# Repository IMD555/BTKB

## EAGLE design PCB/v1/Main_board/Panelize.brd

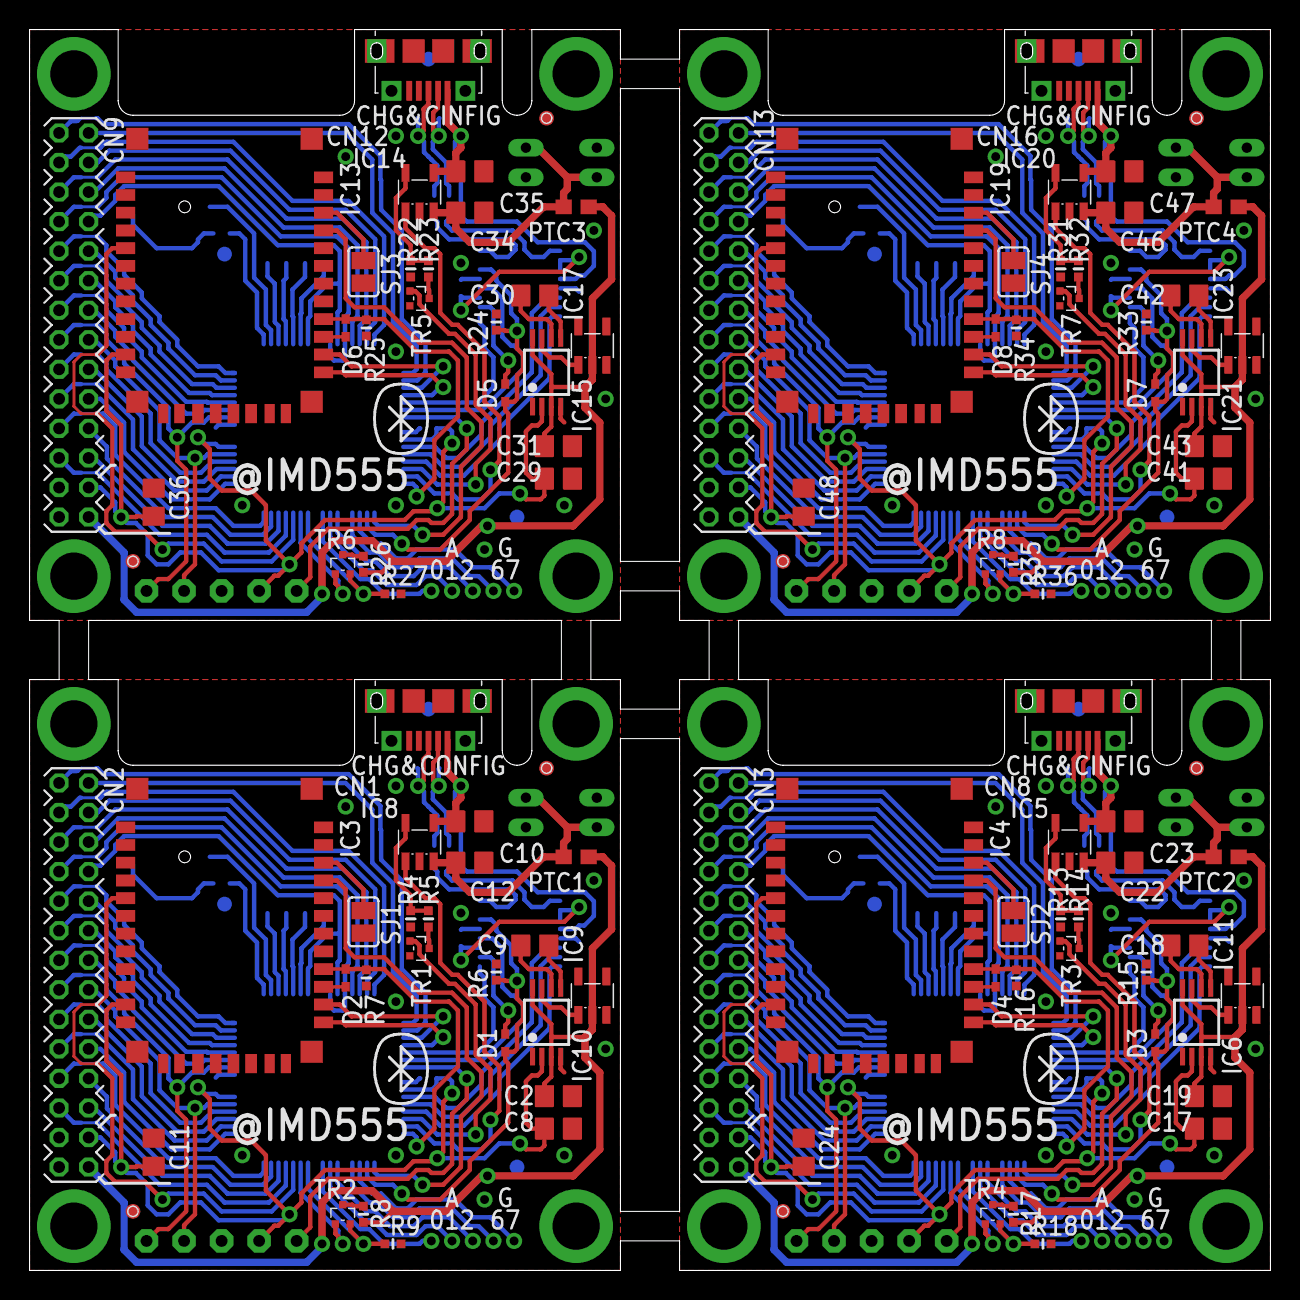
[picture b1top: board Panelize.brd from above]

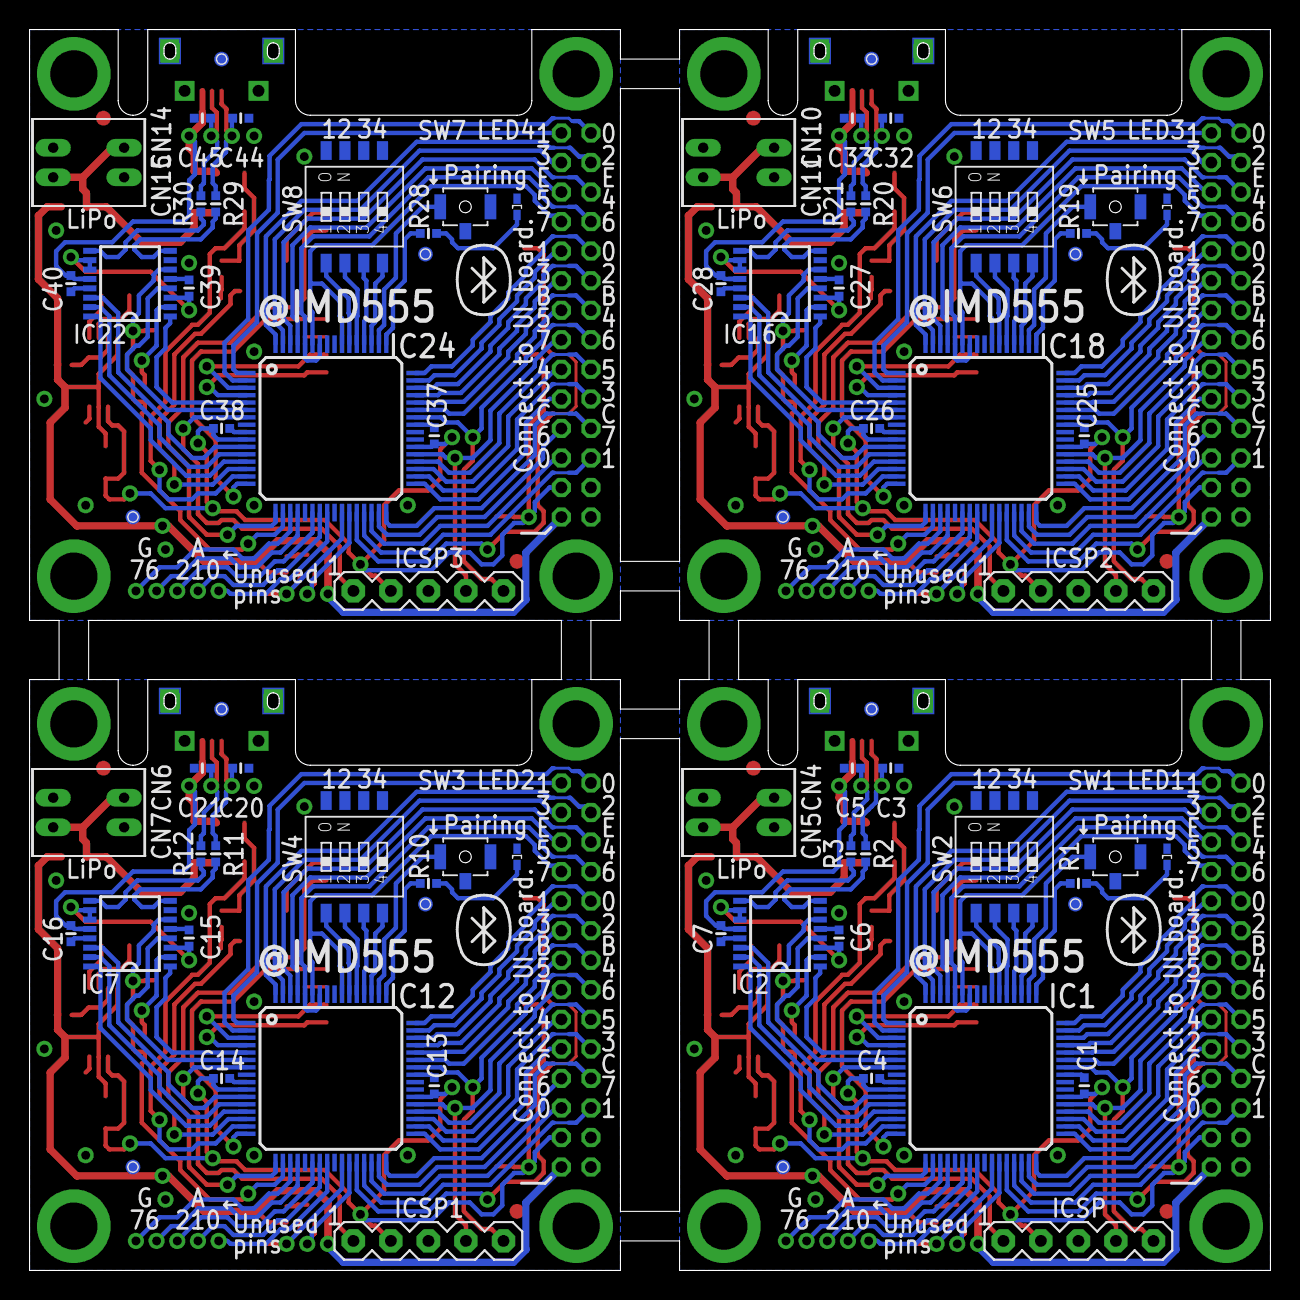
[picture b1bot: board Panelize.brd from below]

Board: 2 copper layers, 84.0 x 84.0 mm, 184 parts (80 on the bottom side), 264 nets.

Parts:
C1, C4, C6, C7, C13, C14, C15, C16, C25, C26, C27, C28, C37, C38, C39, C40: 0.1u; C0402-SS
C2, C8, C10, C11, C12, C17, C19, C22, C23, C24, C29, C31, C34, C35, C36, C41, C43, C46, C47, C48: 4.7u; C0805
C3, C5, C20, C21, C32, C33, C44, C45: 47p; C0402-SS
C9, C18, C30, C42: 1u; C0805
CN1, CN8, CN12, CN16: ZX62M-B-5P10118194-0001LF; 10118194-0001LF
CN2, CN3, CN9, CN13: 2X14; 2MM_14X2
CN4, CN5, CN6, CN7, CN10, CN11, CN14, CN15: PH-2_S
D1, D2, D3, D4, D5, D6, D7, D8: VMN2
IC1, IC12, IC18, IC24: PIC18F67K40; TQFP64-10X10
IC2, IC7, IC16, IC22: FT230X; SSOP16
IC3, IC4, IC13, IC19: RN42; RN-42
IC5, IC8, IC14, IC20: MCP73831; SOT23-5L
IC6, IC10, IC15, IC21: MCP1253-33X50; MSOP8
IC9, IC11, IC17, IC23: BD4931G; SOT23-5L
ICSP, ICSP1, ICSP2, ICSP3: MA05-1
LED1, LED2, LED3, LED4: White; CHIP-LED1005
PTC1, PTC2, PTC3, PTC4: 250mA 100mA 0ZCM0010FF2G; R0603
R1, R10, R19, R28: 100; R0402-SS
R2, R3, R11, R12, R20, R21, R29, R30: 27; R0402-SS
R4, R6, R7, R9, R13, R15, R16, R18, R22, R24, R25, R27, R31, R33, R34, R36: 10k; R0402-SS
R5, R14, R23, R32: 3.3k; R0402-SS
R8, R17, R26, R35: 33k; R0402-SS
SJ1, SJ2, SJ3, SJ4: SJ
SW1, SW3, SW5, SW7: B3U-1000P
SW2, SW4, SW6, SW8: CHS-04B
TR1, TR3, TR5, TR7: DMG1012T-7; SOT523
TR2, TR4, TR6, TR8: DMG1012T; SOT523
U$1, U$2, U$3, U$4, U$5, U$6, U$7, U$8, U$9, U$10, U$11, U$12, U$13, U$14, U$15, U$16, U$17, U$18, U$19, U$20: PCB_CHECK

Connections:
GND: C1.1, C2.2, C3.2, C4.1, C5.2, C6.2, C7.2, C8.2, C10.2, C11.2, C12.2, CN1.P$5, CN1.P$6, CN1.P$7, CN1.S1, CN1.S2, CN1.S3, CN1.S4, CN1.S5, CN1.S6, CN1.S7, CN1.S8, CN1.S9, CN1.S10, CN2.2, CN2.4, CN4.2, CN5.2, IC1.9, IC1.21, IC1.25, IC1.41, IC1.56, IC1.57, IC2.5, IC2.13, IC3.1, IC3.12, IC3.28, IC3.29, IC3.SHIELD, IC3.SHIELD@1, IC3.SHIELD@2, IC3.SHIELD@3, IC8.2, IC9.3, IC10.4, ICSP.3, LED1.C, R4.1, R6.1, R7.2, R9.1, SJ1.2, SW1.P$2, SW1.P$3, SW2.5, SW2.6, SW2.7, SW2.8, TR1.2
GND1: C13.1, C14.1, C15.2, C16.2, C17.2, C19.2, C20.2, C21.2, C22.2, C23.2, C24.2, CN3.2, CN3.4, CN6.2, CN7.2, CN8.P$5, CN8.P$6, CN8.P$7, CN8.S1, CN8.S2, CN8.S3, CN8.S4, CN8.S5, CN8.S6, CN8.S7, CN8.S8, CN8.S9, CN8.S10, IC4.1, IC4.12, IC4.28, IC4.29, IC4.SHIELD, IC4.SHIELD@1, IC4.SHIELD@2, IC4.SHIELD@3, IC5.2, IC6.4, IC7.5, IC7.13, IC11.3, IC12.9, IC12.21, IC12.25, IC12.41, IC12.56, IC12.57, ICSP1.3, LED2.C, R13.1, R15.1, R16.2, R18.1, SJ2.2, SW3.P$2, SW3.P$3, SW4.5, SW4.6, SW4.7, SW4.8, TR3.2
GND2: C25.1, C26.1, C27.2, C28.2, C29.2, C31.2, C32.2, C33.2, C34.2, C35.2, C36.2, CN9.2, CN9.4, CN10.2, CN11.2, CN12.P$5, CN12.P$6, CN12.P$7, CN12.S1, CN12.S2, CN12.S3, CN12.S4, CN12.S5, CN12.S6, CN12.S7, CN12.S8, CN12.S9, CN12.S10, IC13.1, IC13.12, IC13.28, IC13.29, IC13.SHIELD, IC13.SHIELD@1, IC13.SHIELD@2, IC13.SHIELD@3, IC14.2, IC15.4, IC16.5, IC16.13, IC17.3, IC18.9, IC18.21, IC18.25, IC18.41, IC18.56, IC18.57, ICSP2.3, LED3.C, R22.1, R24.1, R25.2, R27.1, SJ3.2, SW5.P$2, SW5.P$3, SW6.5, SW6.6, SW6.7, SW6.8, TR5.2
GND3: C37.1, C38.1, C39.2, C40.2, C41.2, C43.2, C44.2, C45.2, C46.2, C47.2, C48.2, CN13.2, CN13.4, CN14.2, CN15.2, CN16.P$5, CN16.P$6, CN16.P$7, CN16.S1, CN16.S2, CN16.S3, CN16.S4, CN16.S5, CN16.S6, CN16.S7, CN16.S8, CN16.S9, CN16.S10, IC19.1, IC19.12, IC19.28, IC19.29, IC19.SHIELD, IC19.SHIELD@1, IC19.SHIELD@2, IC19.SHIELD@3, IC20.2, IC21.4, IC22.5, IC22.13, IC23.3, IC24.9, IC24.21, IC24.25, IC24.41, IC24.56, IC24.57, ICSP3.3, LED4.C, R31.1, R33.1, R34.2, R36.1, SJ4.2, SW7.P$2, SW7.P$3, SW8.5, SW8.6, SW8.7, SW8.8, TR7.2
unnamed: IC1.4, IC3.13
unnamed: IC1.5, IC2.1
unnamed: IC1.3, IC3.14
unnamed: C16.1, C23.1, CN8.P$1, IC5.4, IC7.12
unnamed: C5.1, CN1.P$3, R2.2
unnamed: C3.1, CN1.P$2, R3.2
unnamed: IC1.6, IC2.4
unnamed: IC12.7, ICSP1.1
unnamed: C7.1, C10.1, CN1.P$1, IC2.12, IC8.4
unnamed: IC1.15, IC8.1
unnamed: IC4.14, IC12.3
unnamed: IC4.13, IC12.4
unnamed: IC7.4, IC12.6
unnamed: IC1.7, ICSP.1
unnamed: IC7.1, IC12.5
unnamed: C18.1, IC6.6
unnamed: C18.2, IC6.5
unnamed: IC12.52, SW4.3
unnamed: IC12.51, SW4.4
unnamed: IC12.50, SW3.P$1
unnamed: IC12.53, SW4.2
unnamed: IC12.54, SW4.1
unnamed: IC12.49, R10.1
unnamed: LED2.A, R10.2
unnamed: IC4.5, IC12.28
unnamed: IC7.9, R12.1
unnamed: IC7.8, R11.1
unnamed: C21.1, CN8.P$3, R11.2
unnamed: C20.1, CN8.P$2, R12.2
unnamed: IC7.15, IC12.12
unnamed: IC7.16, IC12.13
unnamed: IC5.5, R13.2, R14.2
unnamed: IC12.14, TR3.1
unnamed: IC1.54, SW2.1
unnamed: IC1.52, SW2.3
unnamed: C9.1, IC10.6
unnamed: C9.2, IC10.5
unnamed: IC1.51, SW2.4
unnamed: IC1.49, R1.1
unnamed: IC1.28, IC3.5
unnamed: LED1.A, R1.2
unnamed: C6.1, IC2.3, IC2.10, IC2.11
unnamed: IC1.50, SW1.P$1
unnamed: IC2.9, R3.1
unnamed: IC1.53, SW2.2
unnamed: IC2.8, R2.1
unnamed: C15.1, IC7.3, IC7.10, IC7.11
unnamed: IC1.12, IC2.15
unnamed: IC1.13, IC2.16
unnamed: IC8.5, R4.2, R5.2
unnamed: IC1.27, TR2.1
unnamed: D2.C, IC1.16, IC3.16, R7.1
unnamed: IC1.14, TR1.1
unnamed: D2.A, IC3.15
unnamed: IC1.11, IC2.14
unnamed: D1.A, IC2.2
unnamed: D1.C, IC1.18, IC2.6, R6.2
unnamed: IC1.17, IC3.21
unnamed: IC3.22, SJ1.1
unnamed: D4.A, IC4.15
unnamed: IC7.14, IC12.11
unnamed: D3.A, IC7.2
unnamed: D4.C, IC4.16, IC12.16, R16.1
unnamed: D3.C, IC7.6, IC12.18, R15.2
unnamed: IC4.22, SJ2.1
unnamed: IC4.21, IC12.17
unnamed: IC5.1, IC12.15
unnamed: IC12.27, TR4.1
unnamed: IC6.7, IC11.1
unnamed: IC9.1, IC10.7
unnamed: R5.1, TR1.3
unnamed: R8.1, TR2.3
unnamed: IC1.26, R9.2, TR2.2
unnamed: R14.1, TR3.3
unnamed: R17.1, TR4.3
unnamed: IC12.26, R18.2, TR4.2
unnamed: C28.1, C35.1, CN12.P$1, IC14.4, IC16.12
unnamed: IC18.7, ICSP2.1
unnamed: IC13.14, IC18.3
unnamed: IC13.13, IC18.4
unnamed: IC16.4, IC18.6
unnamed: IC16.1, IC18.5
unnamed: C30.1, IC15.6
unnamed: C30.2, IC15.5
unnamed: IC18.52, SW6.3
unnamed: IC18.51, SW6.4
unnamed: IC18.50, SW5.P$1
unnamed: IC18.53, SW6.2
unnamed: IC18.54, SW6.1
unnamed: IC18.49, R19.1
unnamed: LED3.A, R19.2
unnamed: IC13.5, IC18.28
unnamed: IC16.9, R21.1
unnamed: IC16.8, R20.1
unnamed: C33.1, CN12.P$3, R20.2
unnamed: C32.1, CN12.P$2, R21.2
unnamed: IC16.15, IC18.12
unnamed: IC16.16, IC18.13
unnamed: IC14.5, R22.2, R23.2
unnamed: IC18.14, TR5.1
unnamed: C27.1, IC16.3, IC16.10, IC16.11
unnamed: D6.A, IC13.15
unnamed: IC16.14, IC18.11
unnamed: D5.A, IC16.2
unnamed: D6.C, IC13.16, IC18.16, R25.1
unnamed: D5.C, IC16.6, IC18.18, R24.2
unnamed: IC13.22, SJ3.1
unnamed: IC13.21, IC18.17
unnamed: IC14.1, IC18.15
unnamed: IC18.27, TR6.1
unnamed: IC15.7, IC17.1
unnamed: R23.1, TR5.3
unnamed: R26.1, TR6.3
unnamed: IC18.26, R27.2, TR6.2
unnamed: C40.1, C47.1, CN16.P$1, IC20.4, IC22.12
unnamed: IC24.7, ICSP3.1
unnamed: IC19.14, IC24.3
unnamed: IC19.13, IC24.4
unnamed: IC22.4, IC24.6
unnamed: IC22.1, IC24.5
unnamed: C42.1, IC21.6
unnamed: C42.2, IC21.5
unnamed: IC24.52, SW8.3
unnamed: IC24.51, SW8.4
unnamed: IC24.50, SW7.P$1
unnamed: IC24.53, SW8.2
unnamed: IC24.54, SW8.1
unnamed: IC24.49, R28.1
unnamed: LED4.A, R28.2
unnamed: IC19.5, IC24.28
unnamed: IC22.9, R30.1
unnamed: IC22.8, R29.1
unnamed: C45.1, CN16.P$3, R29.2
unnamed: C44.1, CN16.P$2, R30.2
unnamed: IC22.15, IC24.12
unnamed: IC22.16, IC24.13
unnamed: IC20.5, R31.2, R32.2
unnamed: IC24.14, TR7.1
unnamed: C39.1, IC22.3, IC22.10, IC22.11
unnamed: D8.A, IC19.15
unnamed: IC22.14, IC24.11
unnamed: D7.A, IC22.2
unnamed: D8.C, IC19.16, IC24.16, R34.1
unnamed: D7.C, IC22.6, IC24.18, R33.2
unnamed: IC19.22, SJ4.1
unnamed: IC19.21, IC24.17
unnamed: IC20.1, IC24.15
unnamed: IC24.27, TR8.1
unnamed: IC21.7, IC23.1
unnamed: R32.1, TR7.3
unnamed: R35.1, TR8.3
unnamed: IC24.26, R36.2, TR8.2
RB0: CN2.20, IC1.48
RB1: CN2.19, IC1.47
RB2: CN2.18, IC1.46
RB3: CN2.17, IC1.45
RB4: CN2.16, IC1.44
RB5: CN2.15, IC1.43
RB6: CN2.14, IC1.42, ICSP.5
RB7: CN2.13, IC1.37, ICSP.4
RB8: CN3.20, IC12.48
RB9: CN3.19, IC12.47
RB10: CN3.18, IC12.46
RB11: CN3.17, IC12.45
RB12: CN3.16, IC12.44
RB13: CN3.15, IC12.43
RB14: CN3.14, IC12.42, ICSP1.5
RB15: CN3.13, IC12.37, ICSP1.4
RB16: CN9.20, IC18.48
RB17: CN9.19, IC18.47
RB18: CN9.18, IC18.46
RB19: CN9.17, IC18.45
RB20: CN9.16, IC18.44
RB21: CN9.15, IC18.43
RB22: CN9.14, IC18.42, ICSP2.5
RB23: CN9.13, IC18.37, ICSP2.4
RB24: CN13.20, IC24.48
RB25: CN13.19, IC24.47
RB26: CN13.18, IC24.46
RB27: CN13.17, IC24.45
RB28: CN13.16, IC24.44
RB29: CN13.15, IC24.43
RB30: CN13.14, IC24.42, ICSP3.5
RB31: CN13.13, IC24.37, ICSP3.4
RC0: CN2.5, IC1.30
RC1: CN2.6, IC1.29
RC2: CN2.9, IC1.33
RC3: CN2.10, IC1.34
RC4: CN2.11, IC1.35
RC5: CN2.12, IC1.36
RC6: CN2.7, IC1.31
RC7: CN2.8, IC1.32
RC8: CN3.12, IC12.36
RC9: CN3.11, IC12.35
RC10: CN3.10, IC12.34
RC11: CN3.9, IC12.33
RC12: CN3.8, IC12.32
RC13: CN3.7, IC12.31
RC14: CN3.5, IC12.30
RC15: CN3.6, IC12.29
RC16: CN9.12, IC18.36
RC17: CN9.11, IC18.35
RC18: CN9.10, IC18.34
RC19: CN9.9, IC18.33
RC20: CN9.8, IC18.32
RC21: CN9.7, IC18.31
RC22: CN9.5, IC18.30
RC23: CN9.6, IC18.29
RC24: CN13.12, IC24.36
RC25: CN13.11, IC24.35
RC26: CN13.10, IC24.34
RC27: CN13.9, IC24.33
RC28: CN13.8, IC24.32
RC29: CN13.7, IC24.31
RC30: CN13.5, IC24.30
RC31: CN13.6, IC24.29
RE0: CN2.28, IC1.2
RE1: CN2.27, IC1.1
RE2: CN2.26, IC1.64
RE3: CN2.25, IC1.63
RE4: CN2.24, IC1.62
RE5: CN2.23, IC1.61
RE6: CN2.22, IC1.58, IC1.60
RE7: CN2.21, IC1.55, IC1.59
RE8: CN3.21, IC12.55, IC12.59
RE9: CN3.22, IC12.58, IC12.60
RE10: CN3.23, IC12.61
RE11: CN3.24, IC12.62
RE12: CN3.25, IC12.63
RE13: CN3.26, IC12.64
RE14: CN3.27, IC12.1
RE15: CN3.28, IC12.2
RE16: CN9.21, IC18.55, IC18.59
RE17: CN9.22, IC18.58, IC18.60
RE18: CN9.23, IC18.61
RE19: CN9.24, IC18.62
RE20: CN9.25, IC18.63
RE21: CN9.26, IC18.64
RE22: CN9.27, IC18.1
RE23: CN9.28, IC18.2
RE24: CN13.21, IC24.55, IC24.59
RE25: CN13.22, IC24.58, IC24.60
RE26: CN13.23, IC24.61
RE27: CN13.24, IC24.62
RE28: CN13.25, IC24.63
RE29: CN13.26, IC24.64
RE30: CN13.27, IC24.1
RE31: CN13.28, IC24.2
VBAT: C12.1, CN4.1, CN5.1, IC8.3, PTC1.1
VBAT1: C19.1, CN3.1, IC6.3, IC6.8, IC11.2, PTC2.2, R17.2
VBAT2: C2.1, CN2.1, IC9.2, IC10.3, IC10.8, PTC1.2, R8.2
VBAT3: C22.1, CN6.1, CN7.1, IC5.3, PTC2.1
VBAT4: C31.1, CN9.1, IC15.3, IC15.8, IC17.2, PTC3.2, R26.2
VBAT5: C34.1, CN10.1, CN11.1, IC14.3, PTC3.1
VBAT6: C43.1, CN13.1, IC21.3, IC21.8, IC23.2, PTC4.2, R35.2
VBAT7: C46.1, CN14.1, CN15.1, IC20.3, PTC4.1
VDD: C1.2, C4.2, C8.1, C11.1, CN2.3, IC1.10, IC1.38, IC3.11, IC10.2, ICSP.2
VDD1: C13.2, C14.2, C17.1, C24.1, CN3.3, IC4.11, IC6.2, IC12.10, IC12.38, ICSP1.2
VDD2: C25.2, C26.2, C29.1, C36.1, CN9.3, IC13.11, IC15.2, IC18.10, IC18.38, ICSP2.2
VDD3: C37.2, C38.2, C41.1, C48.1, CN13.3, IC19.11, IC21.2, IC24.10, IC24.38, ICSP3.2

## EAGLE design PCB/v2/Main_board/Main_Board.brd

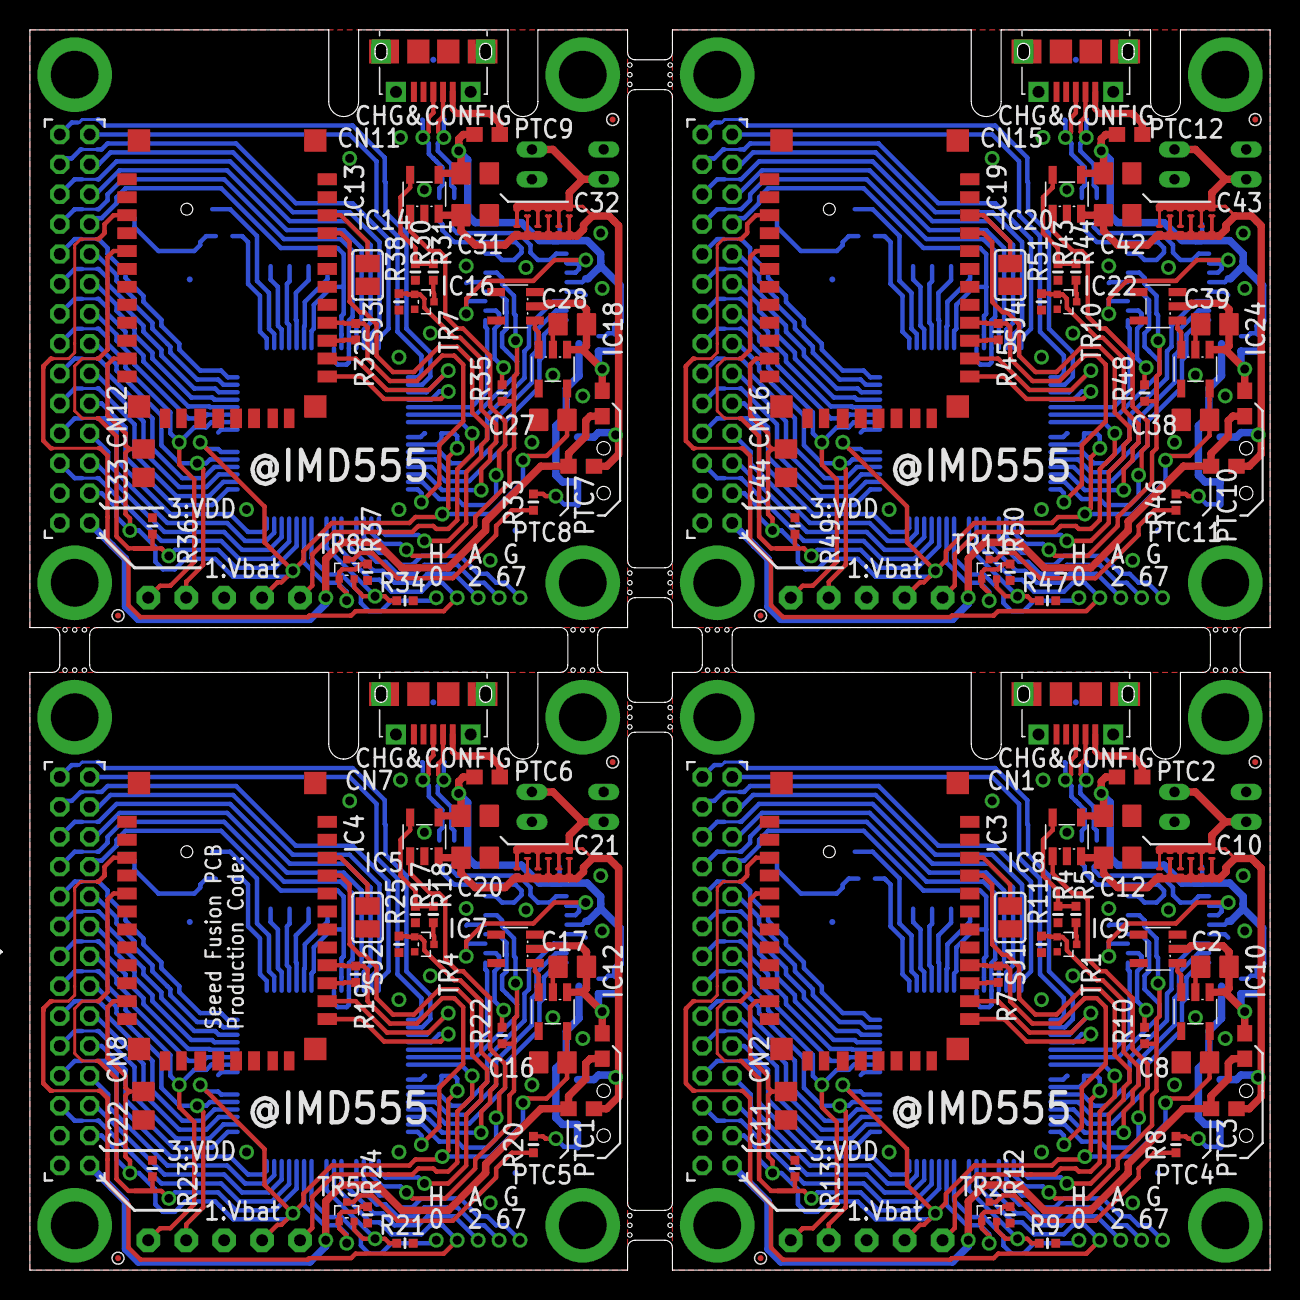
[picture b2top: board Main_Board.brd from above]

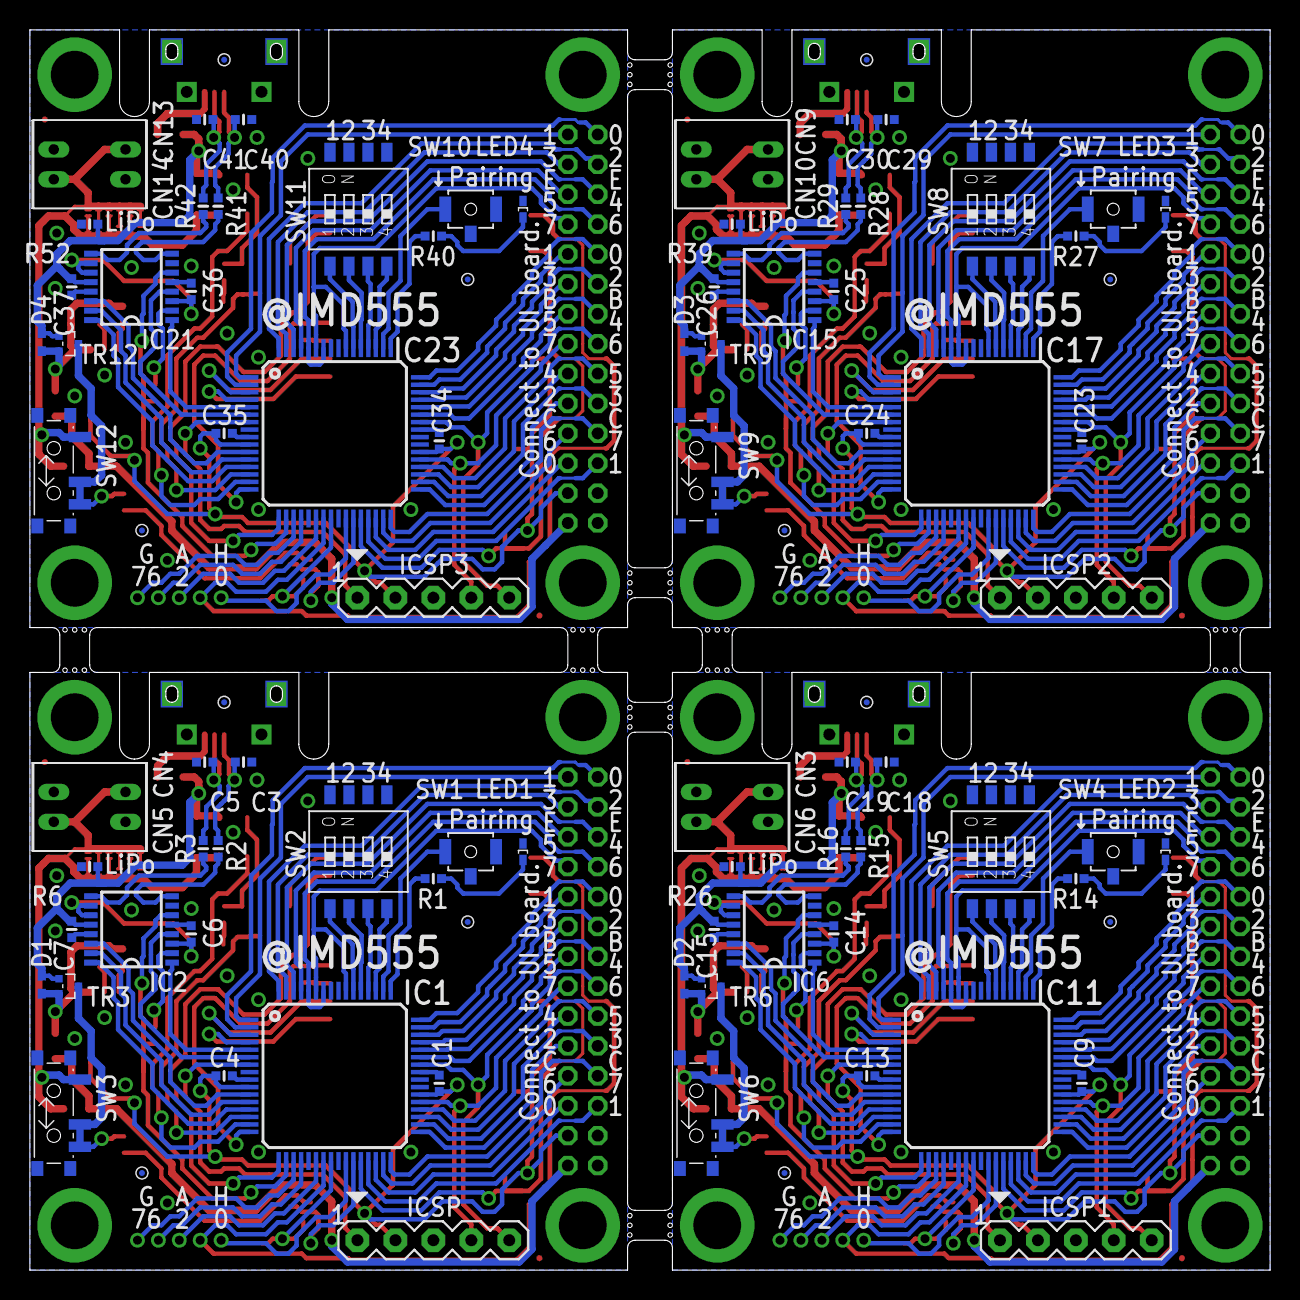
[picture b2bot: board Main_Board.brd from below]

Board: 2 copper layers, 83.0 x 83.0 mm, 232 parts (96 on the bottom side), 272 nets.

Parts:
C1, C4, C6, C7, C9, C13, C14, C15, C23, C24, C25, C26, C34, C35, C36, C37: 0.1u; C0402-SS
C2, C8, C10, C11, C12, C16, C17, C20, C21, C22, C27, C28, C31, C32, C33, C38, C39, C42, C43, C44: 4.7u; C0805
C3, C5, C18, C19, C29, C30, C40, C41: 47p; C0402-SS
CN1, CN7, CN11, CN15: microUSB; 10118194-0001LF
CN2, CN8, CN12, CN16: 2X14R; 2MM_14X2_R
CN3, CN4, CN5, CN6, CN9, CN10, CN13, CN14: PH-2_S
D1, D2, D3, D4: VMN2
F1, F2, F3, F4, F5, F6, F7, F8, F9, F10, F11, F12, F13, F14, F15, F16, F17, F18, F19, F20, F21, F22, F23, F24: FUSEPAT0.2; FUSE_PAT1
IC1, IC11, IC17, IC23: PIC18LF67K40; TQFP64-10X10
IC2, IC6, IC15, IC21: FT230X; SSOP16
IC3, IC4, IC13, IC19: RN42; RN-42
IC5, IC8, IC14, IC20: MCP73832; SOT23-5L
IC7, IC9, IC16, IC22: BD4931G; SOT23-5L
IC10, IC12, IC18, IC24: NCP551; SOT23-5L
ICSP, ICSP1, ICSP2, ICSP3: (Not mounting); MA05-1
LED1, LED2, LED3, LED4: Blue; CHIP-LED1005
PTC1, PTC2, PTC3, PTC4, PTC5, PTC6, PTC7, PTC8, PTC9, PTC10, PTC11, PTC12: 250mA 100mA 0ZCM0010FF2G; R0603
R1, R14, R27, R40: 1000 or 330; R0402-SS
R2, R3, R15, R16, R28, R29, R41, R42: 27; R0402-SS
R4, R7, R9, R10, R17, R19, R21, R22, R30, R32, R34, R35, R43, R45, R47, R48: 10k; R0402-SS
R5, R18, R31, R44: 3.3k; R0402-SS
R6, R8, R20, R26, R33, R39, R46, R52: 33k; R0402-SS
R11, R12, R13, R23, R24, R25, R36, R37, R38, R49, R50, R51: 100k; R0402-SS
SJ1, SJ2, SJ3, SJ4: (Don't short); SJ
SW1, SW4, SW7, SW10: B3U-1100P-B
SW2, SW5, SW8, SW11: CHS-04B
SW3, SW6, SW9, SW12: MA12R
TR1, TR2, TR4, TR5, TR7, TR8, TR10, TR11: DMG1012T-7; SOT523
TR3, TR6, TR9, TR12: PMOSSOT523; SOT523
U$1, U$2, U$3, U$4, U$5, U$6, U$7, U$8, U$9, U$10, U$11, U$12, U$13, U$14, U$15, U$16, U$17, U$18, U$19, U$20: PCB_CHECK

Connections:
GND: C1.1, C2.2, C3.2, C4.1, C5.2, C6.2, C7.2, C8.2, C10.2, C11.2, C12.2, CN1.P$5, CN1.P$6, CN1.P$7, CN1.S1, CN1.S2, CN1.S3, CN1.S4, CN1.S5, CN1.S6, CN1.S7, CN1.S8, CN1.S9, CN1.S10, CN2.2, CN2.4, CN4.2, CN5.2, IC1.8, IC1.9, IC1.21, IC1.25, IC1.39, IC1.40, IC1.41, IC1.56, IC1.57, IC2.5, IC2.13, IC3.1, IC3.12, IC3.28, IC3.29, IC3.SHIELD, IC3.SHIELD@1, IC3.SHIELD@2, IC3.SHIELD@3, IC8.2, IC9.3, IC10.2, ICSP.3, LED1.C, R4.1, R6.1, R9.1, R11.1, R12.1, R13.2, SJ1.2, SW1.P$2, SW1.P$3, SW2.5, SW2.6, SW2.7, SW2.8, SW3.P$4, SW3.P$5, SW3.P$6, SW3.P$7, TR1.2
GND1: C9.1, C13.1, C14.2, C15.2, C16.2, C17.2, C18.2, C19.2, C20.2, C21.2, C22.2, CN3.2, CN6.2, CN7.P$5, CN7.P$6, CN7.P$7, CN7.S1, CN7.S2, CN7.S3, CN7.S4, CN7.S5, CN7.S6, CN7.S7, CN7.S8, CN7.S9, CN7.S10, CN8.2, CN8.4, IC4.1, IC4.12, IC4.28, IC4.29, IC4.SHIELD, IC4.SHIELD@1, IC4.SHIELD@2, IC4.SHIELD@3, IC5.2, IC6.5, IC6.13, IC7.3, IC11.8, IC11.9, IC11.21, IC11.25, IC11.39, IC11.40, IC11.41, IC11.56, IC11.57, IC12.2, ICSP1.3, LED2.C, R17.1, R21.1, R23.2, R24.1, R25.1, R26.1, SJ2.2, SW4.P$2, SW4.P$3, SW5.5, SW5.6, SW5.7, SW5.8, SW6.P$4, SW6.P$5, SW6.P$6, SW6.P$7, TR4.2
GND2: C23.1, C24.1, C25.2, C26.2, C27.2, C28.2, C29.2, C30.2, C31.2, C32.2, C33.2, CN9.2, CN10.2, CN11.P$5, CN11.P$6, CN11.P$7, CN11.S1, CN11.S2, CN11.S3, CN11.S4, CN11.S5, CN11.S6, CN11.S7, CN11.S8, CN11.S9, CN11.S10, CN12.2, CN12.4, IC13.1, IC13.12, IC13.28, IC13.29, IC13.SHIELD, IC13.SHIELD@1, IC13.SHIELD@2, IC13.SHIELD@3, IC14.2, IC15.5, IC15.13, IC16.3, IC17.8, IC17.9, IC17.21, IC17.25, IC17.39, IC17.40, IC17.41, IC17.56, IC17.57, IC18.2, ICSP2.3, LED3.C, R30.1, R34.1, R36.2, R37.1, R38.1, R39.1, SJ3.2, SW7.P$2, SW7.P$3, SW8.5, SW8.6, SW8.7, SW8.8, SW9.P$4, SW9.P$5, SW9.P$6, SW9.P$7, TR7.2
GND3: C34.1, C35.1, C36.2, C37.2, C38.2, C39.2, C40.2, C41.2, C42.2, C43.2, C44.2, CN13.2, CN14.2, CN15.P$5, CN15.P$6, CN15.P$7, CN15.S1, CN15.S2, CN15.S3, CN15.S4, CN15.S5, CN15.S6, CN15.S7, CN15.S8, CN15.S9, CN15.S10, CN16.2, CN16.4, IC19.1, IC19.12, IC19.28, IC19.29, IC19.SHIELD, IC19.SHIELD@1, IC19.SHIELD@2, IC19.SHIELD@3, IC20.2, IC21.5, IC21.13, IC22.3, IC23.8, IC23.9, IC23.21, IC23.25, IC23.39, IC23.40, IC23.41, IC23.56, IC23.57, IC24.2, ICSP3.3, LED4.C, R43.1, R47.1, R49.2, R50.1, R51.1, R52.1, SJ4.2, SW10.P$2, SW10.P$3, SW11.5, SW11.6, SW11.7, SW11.8, SW12.P$4, SW12.P$5, SW12.P$6, SW12.P$7, TR10.2
unnamed: IC1.4, IC3.13
unnamed: IC1.5, IC2.1
unnamed: IC1.3, IC3.14
unnamed: C5.1, CN1.P$3, R2.2
unnamed: C3.1, CN1.P$2, R3.2
unnamed: IC1.6, IC2.4
unnamed: CN2.1, PTC3.2, PTC4.2
unnamed: C7.1, C10.1, D1.A, IC2.12, IC8.4, PTC2.2, R6.2, TR3.1
unnamed: IC1.15, IC8.1
unnamed: IC11.7, ICSP1.1
unnamed: C12.1, CN4.1, CN5.1, F1.P$1, F1.P$2, F2.P$1, F2.P$2, F3.P$1, F3.P$2, F4.P$1, F4.P$2, F5.P$1, F5.P$2, F6.P$1, F6.P$2, IC8.3, PTC4.1, SW3.P$1
unnamed: R8.2, SW3.P$2, SW3.P$3, TR3.3
unnamed: IC1.7, ICSP.1
unnamed: CN1.P$1, PTC2.1
unnamed: IC4.14, IC11.3
unnamed: IC4.13, IC11.4
unnamed: IC6.4, IC11.6
unnamed: IC6.1, IC11.5
unnamed: IC11.52, SW5.3
unnamed: IC11.51, SW5.4
unnamed: IC11.50, SW4.P$1
unnamed: IC11.53, SW5.2
unnamed: IC11.54, SW5.1
unnamed: IC11.49, R14.1
unnamed: LED2.A, R14.2
unnamed: IC4.5, IC11.28, R23.1
unnamed: IC6.9, R16.1
unnamed: IC6.8, R15.1
unnamed: C19.1, CN7.P$3, R15.2
unnamed: C18.1, CN7.P$2, R16.2
unnamed: IC6.15, IC11.12
unnamed: IC6.16, IC11.13
unnamed: IC1.54, SW2.1
unnamed: IC1.52, SW2.3
unnamed: IC5.5, R17.2, R18.2
unnamed: IC11.14, R25.2, TR4.1
unnamed: IC1.51, SW2.4
unnamed: IC1.49, R1.1
unnamed: IC1.28, IC3.5, R13.1
unnamed: LED1.A, R1.2
unnamed: C6.1, IC2.3, IC2.10, IC2.11
unnamed: IC1.50, SW1.P$1
unnamed: IC2.9, R3.1
unnamed: IC1.53, SW2.2
unnamed: IC2.8, R2.1
unnamed: C14.1, IC6.3, IC6.10, IC6.11
unnamed: IC1.12, IC2.15
unnamed: IC1.13, IC2.16
unnamed: IC8.5, R4.2, R5.2
unnamed: IC1.27, R12.2, TR2.1
unnamed: IC1.16, IC3.16, R7.1
unnamed: IC1.14, R11.2, TR1.1
unnamed: IC3.15, R7.2
unnamed: IC1.11, IC2.14
unnamed: IC2.2, R10.2
unnamed: IC1.18, IC2.6, R10.1
unnamed: IC1.17, IC3.21
unnamed: IC3.22, SJ1.1
unnamed: IC4.15, R19.2
unnamed: IC6.14, IC11.11
unnamed: IC6.2, R22.2
unnamed: IC4.16, IC11.16, R19.1
unnamed: IC6.6, IC11.18, R22.1
unnamed: IC4.22, SJ2.1
unnamed: IC4.21, IC11.17
unnamed: IC5.1, IC11.15
unnamed: IC11.27, R24.2, TR5.1
unnamed: IC7.1, IC12.3
unnamed: IC9.1, IC10.3
unnamed: R5.1, TR1.3
unnamed: R8.1, TR2.3
unnamed: IC1.24, R9.2, TR2.2
unnamed: R18.1, TR4.3
unnamed: R20.1, TR5.3
unnamed: IC4.3, IC11.23
unnamed: IC11.24, R21.2, TR5.2
unnamed: CN8.1, PTC1.2, PTC5.2
unnamed: C20.1, CN3.1, CN6.1, F7.P$1, F7.P$2, F8.P$1, F8.P$2, F9.P$1, F9.P$2, F10.P$1, F10.P$2, F11.P$1, F11.P$2, F12.P$1, F12.P$2, IC5.3, PTC5.1, SW6.P$1
unnamed: C15.1, C21.1, D2.A, IC5.4, IC6.12, PTC6.2, R26.2, TR6.1
unnamed: R20.2, SW6.P$2, SW6.P$3, TR6.3
unnamed: CN7.P$1, PTC6.1
unnamed: IC17.7, ICSP2.1
unnamed: IC13.14, IC17.3
unnamed: IC13.13, IC17.4
unnamed: IC15.4, IC17.6
unnamed: IC15.1, IC17.5
unnamed: IC17.52, SW8.3
unnamed: IC1.23, IC3.3
unnamed: IC17.51, SW8.4
unnamed: IC17.50, SW7.P$1
unnamed: IC17.53, SW8.2
unnamed: IC17.54, SW8.1
unnamed: IC17.49, R27.1
unnamed: LED3.A, R27.2
unnamed: IC13.5, IC17.28, R36.1
unnamed: IC15.9, R29.1
unnamed: IC15.8, R28.1
unnamed: C30.1, CN11.P$3, R28.2
unnamed: C29.1, CN11.P$2, R29.2
unnamed: IC15.15, IC17.12
unnamed: IC15.16, IC17.13
unnamed: IC14.5, R30.2, R31.2
unnamed: IC17.14, R38.2, TR7.1
unnamed: C25.1, IC15.3, IC15.10, IC15.11
unnamed: IC13.15, R32.2
unnamed: IC15.14, IC17.11
unnamed: IC15.2, R35.2
unnamed: IC13.16, IC17.16, R32.1
unnamed: IC15.6, IC17.18, R35.1
unnamed: IC13.22, SJ3.1
unnamed: IC13.21, IC17.17
unnamed: IC14.1, IC17.15
unnamed: IC17.27, R37.2, TR8.1
unnamed: IC16.1, IC18.3
unnamed: R31.1, TR7.3
unnamed: R33.1, TR8.3
unnamed: IC13.3, IC17.23
unnamed: IC17.24, R34.2, TR8.2
unnamed: CN12.1, PTC7.2, PTC8.2
unnamed: C31.1, CN9.1, CN10.1, F13.P$1, F13.P$2, F14.P$1, F14.P$2, F15.P$1, F15.P$2, F16.P$1, F16.P$2, F17.P$1, F17.P$2, F18.P$1, F18.P$2, IC14.3, PTC8.1, SW9.P$1
unnamed: C26.1, C32.1, D3.A, IC14.4, IC15.12, PTC9.2, R39.2, TR9.1
unnamed: R33.2, SW9.P$2, SW9.P$3, TR9.3
unnamed: CN11.P$1, PTC9.1
unnamed: IC23.7, ICSP3.1
unnamed: IC19.14, IC23.3
unnamed: IC19.13, IC23.4
unnamed: IC21.4, IC23.6
unnamed: IC21.1, IC23.5
unnamed: IC23.52, SW11.3
unnamed: IC23.51, SW11.4
unnamed: IC23.50, SW10.P$1
unnamed: IC23.53, SW11.2
unnamed: IC23.54, SW11.1
unnamed: IC23.49, R40.1
unnamed: LED4.A, R40.2
unnamed: IC19.5, IC23.28, R49.1
unnamed: IC21.9, R42.1
unnamed: IC21.8, R41.1
unnamed: C41.1, CN15.P$3, R41.2
unnamed: C40.1, CN15.P$2, R42.2
unnamed: IC21.15, IC23.12
unnamed: IC21.16, IC23.13
unnamed: IC20.5, R43.2, R44.2
unnamed: IC23.14, R51.2, TR10.1
unnamed: C36.1, IC21.3, IC21.10, IC21.11
unnamed: IC19.15, R45.2
unnamed: IC21.14, IC23.11
unnamed: IC21.2, R48.2
unnamed: IC19.16, IC23.16, R45.1
unnamed: IC21.6, IC23.18, R48.1
unnamed: IC19.22, SJ4.1
unnamed: IC19.21, IC23.17
unnamed: IC20.1, IC23.15
unnamed: IC23.27, R50.2, TR11.1
unnamed: IC22.1, IC24.3
unnamed: R44.1, TR10.3
unnamed: R46.1, TR11.3
unnamed: IC19.3, IC23.23
unnamed: IC23.24, R47.2, TR11.2
unnamed: CN16.1, PTC10.2, PTC11.2
unnamed: C42.1, CN13.1, CN14.1, F19.P$1, F19.P$2, F20.P$1, F20.P$2, F21.P$1, F21.P$2, F22.P$1, F22.P$2, F23.P$1, F23.P$2, F24.P$1, F24.P$2, IC20.3, PTC11.1, SW12.P$1
unnamed: C37.1, C43.1, D4.A, IC20.4, IC21.12, PTC12.2, R52.2, TR12.1
unnamed: R46.2, SW12.P$2, SW12.P$3, TR12.3
unnamed: CN15.P$1, PTC12.1
RB0: CN2.20, IC1.48
RB1: CN2.19, IC1.47
RB2: CN2.18, IC1.46
RB3: CN2.17, IC1.45
RB4: CN2.16, IC1.44
RB5: CN2.15, IC1.43
RB6: CN2.14, IC1.42, ICSP.5
RB7: CN2.13, IC1.37, ICSP.4
RB8: CN8.20, IC11.48
RB9: CN8.19, IC11.47
RB10: CN8.18, IC11.46
RB11: CN8.17, IC11.45
RB12: CN8.16, IC11.44
RB13: CN8.15, IC11.43
RB14: CN8.14, IC11.42, ICSP1.5
RB15: CN8.13, IC11.37, ICSP1.4
RB16: CN12.20, IC17.48
RB17: CN12.19, IC17.47
RB18: CN12.18, IC17.46
RB19: CN12.17, IC17.45
RB20: CN12.16, IC17.44
RB21: CN12.15, IC17.43
RB22: CN12.14, IC17.42, ICSP2.5
RB23: CN12.13, IC17.37, ICSP2.4
RB24: CN16.20, IC23.48
RB25: CN16.19, IC23.47
RB26: CN16.18, IC23.46
RB27: CN16.17, IC23.45
RB28: CN16.16, IC23.44
RB29: CN16.15, IC23.43
RB30: CN16.14, IC23.42, ICSP3.5
RB31: CN16.13, IC23.37, ICSP3.4
RC0: CN2.5, IC1.30
RC1: CN2.6, IC1.29
RC2: CN2.9, IC1.33
RC3: CN2.10, IC1.34
RC4: CN2.11, IC1.35
RC5: CN2.12, IC1.36
RC6: CN2.7, IC1.31
RC7: CN2.8, IC1.32
RC8: CN8.12, IC11.36
RC9: CN8.11, IC11.35
RC10: CN8.10, IC11.34
RC11: CN8.9, IC11.33
RC12: CN8.8, IC11.32
RC13: CN8.7, IC11.31
RC14: CN8.5, IC11.30
RC15: CN8.6, IC11.29
RC16: CN12.12, IC17.36
RC17: CN12.11, IC17.35
RC18: CN12.10, IC17.34
RC19: CN12.9, IC17.33
RC20: CN12.8, IC17.32
RC21: CN12.7, IC17.31
RC22: CN12.5, IC17.30
RC23: CN12.6, IC17.29
RC24: CN16.12, IC23.36
RC25: CN16.11, IC23.35
RC26: CN16.10, IC23.34
RC27: CN16.9, IC23.33
RC28: CN16.8, IC23.32
RC29: CN16.7, IC23.31
RC30: CN16.5, IC23.30
RC31: CN16.6, IC23.29
RE0: CN2.28, IC1.2
RE1: CN2.27, IC1.1
RE2: CN2.26, IC1.64
RE3: CN2.25, IC1.63
RE4: CN2.24, IC1.62
RE5: CN2.23, IC1.61
RE6: CN2.22, IC1.58, IC1.60
RE7: CN2.21, IC1.55, IC1.59
RE8: CN8.21, IC11.55, IC11.59
RE9: CN8.22, IC11.58, IC11.60
RE10: CN8.23, IC11.61
RE11: CN8.24, IC11.62
RE12: CN8.25, IC11.63
RE13: CN8.26, IC11.64
RE14: CN8.27, IC11.1
RE15: CN8.28, IC11.2
RE16: CN12.21, IC17.55, IC17.59
RE17: CN12.22, IC17.58, IC17.60
RE18: CN12.23, IC17.61
RE19: CN12.24, IC17.62
RE20: CN12.25, IC17.63
RE21: CN12.26, IC17.64
RE22: CN12.27, IC17.1
RE23: CN12.28, IC17.2
RE24: CN16.21, IC23.55, IC23.59
RE25: CN16.22, IC23.58, IC23.60
RE26: CN16.23, IC23.61
RE27: CN16.24, IC23.62
RE28: CN16.25, IC23.63
RE29: CN16.26, IC23.64
RE30: CN16.27, IC23.1
RE31: CN16.28, IC23.2
VBAT: C2.1, D1.C, IC9.2, IC10.1, PTC3.1, TR3.2
VBAT1: C17.1, D2.C, IC7.2, IC12.1, PTC1.1, TR6.2
VBAT2: C28.1, D3.C, IC16.2, IC18.1, PTC7.1, TR9.2
VBAT3: C39.1, D4.C, IC22.2, IC24.1, PTC10.1, TR12.2
VDD: C1.2, C4.2, C8.1, C11.1, CN2.3, IC1.10, IC1.38, IC3.11, IC10.5, ICSP.2
VDD1: C9.2, C13.2, C16.1, C22.1, CN8.3, IC4.11, IC11.10, IC11.38, IC12.5, ICSP1.2
VDD2: C23.2, C24.2, C27.1, C33.1, CN12.3, IC13.11, IC17.10, IC17.38, IC18.5, ICSP2.2
VDD3: C34.2, C35.2, C38.1, C44.1, CN16.3, IC19.11, IC23.10, IC23.38, IC24.5, ICSP3.2
